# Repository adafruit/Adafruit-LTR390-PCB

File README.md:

## Adafruit LTR390 UV and Ambient Light Sensor PCB

<a href="http://www.adafruit.com/products/4831"><br/>
Click here to purchase one from the Adafruit shop</a>

PCB files for the Adafruit LTR390 UV and Ambient Light Sensor. 

Format is EagleCAD schematic and board layout
* https://www.adafruit.com/product/4831

### Description

INSERT PRODUCT COPY HERE

### License

Adafruit invests time and resources providing this open source design, please support Adafruit and open-source hardware by purchasing products from [Adafruit](https://www.adafruit.com)!

Designed by Limor Fried/Ladyada for Adafruit Industries.

Creative Commons Attribution/Share-Alike, all text above must be included in any redistribution. 
See license.txt for additional details.

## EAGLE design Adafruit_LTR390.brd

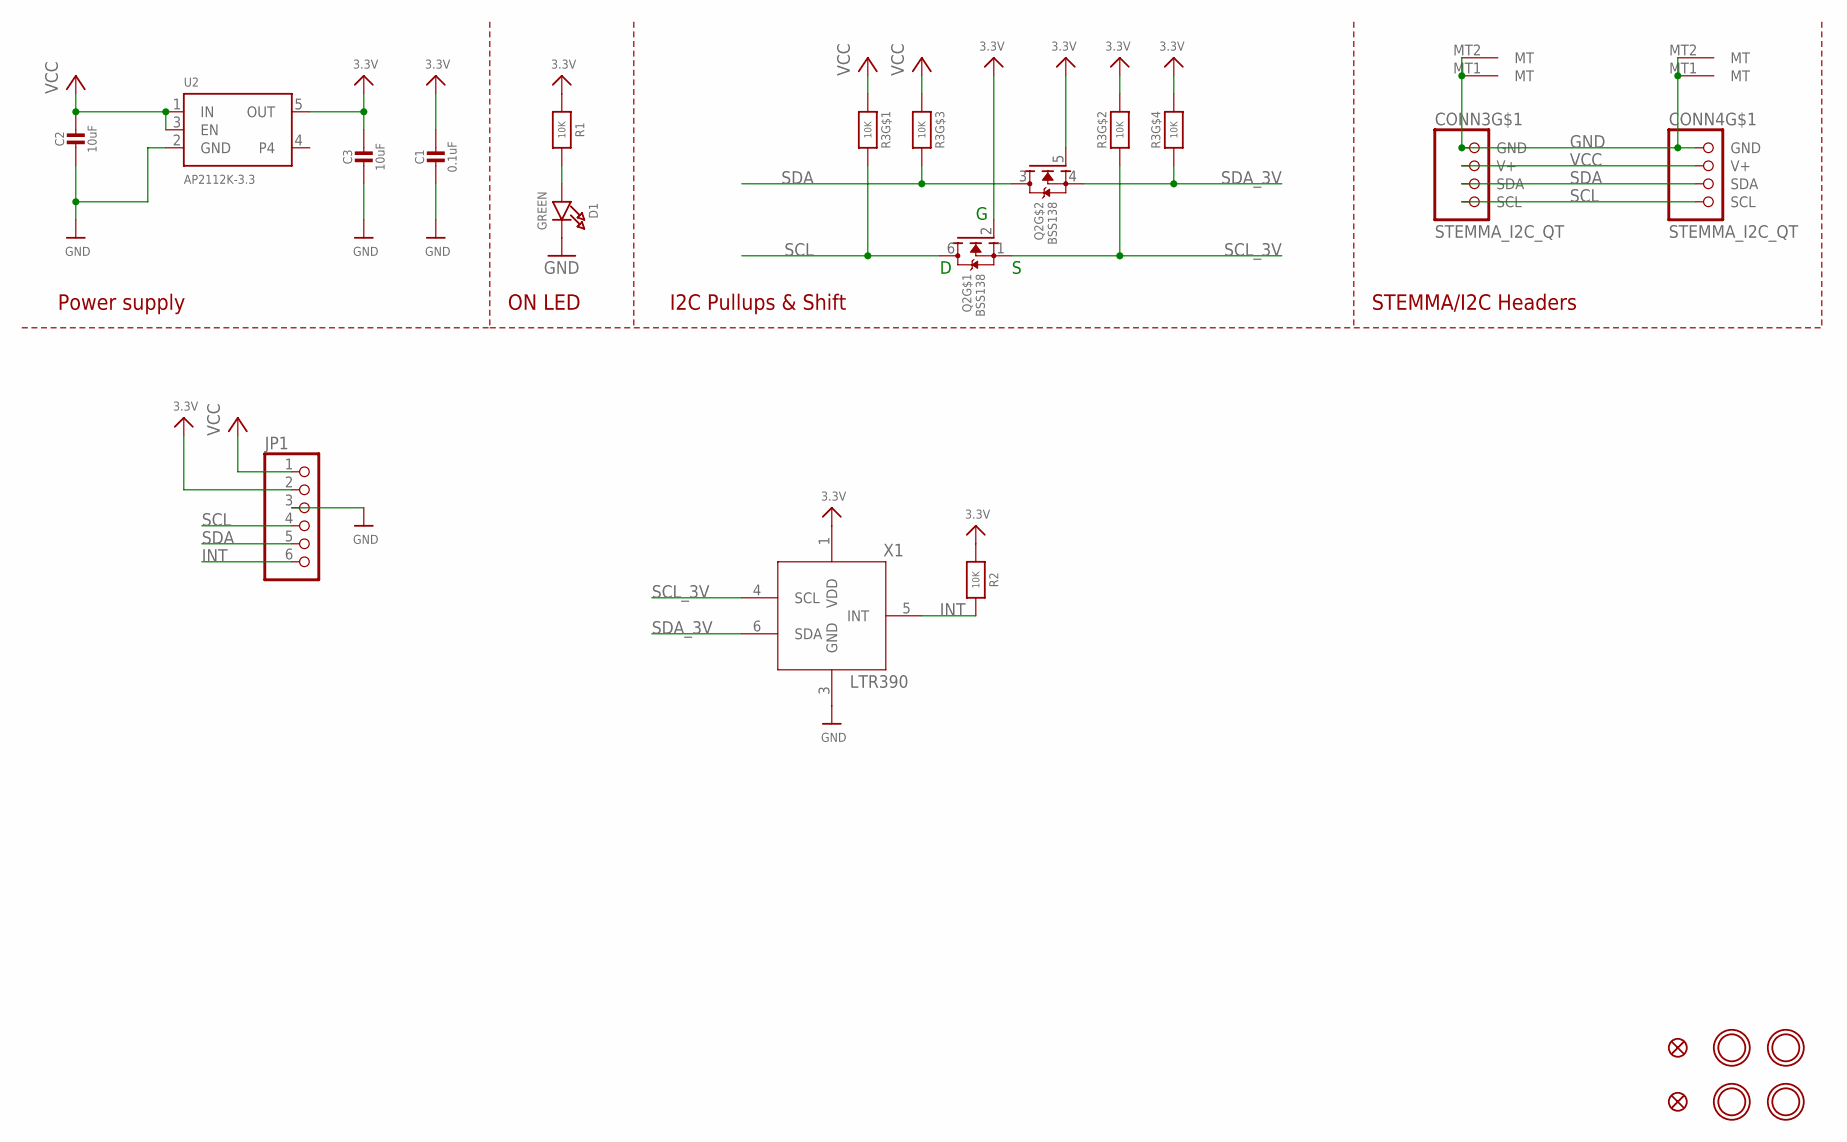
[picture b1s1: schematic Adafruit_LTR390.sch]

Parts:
C1: 0.1uF; 0603-NO
C2, C3: 10uF; 0805-NO
CONN3, CONN4: STEMMA_I2C_QT; JST_SH4
D1: GREEN; CHIPLED_0603_NOOUTLINE
FID3, FID4: FIDUCIAL_1MM
JP1: HEADER-1X670MIL; 1X06_ROUND_70
Q2: BSS138; SOT363
R1, R2: 10K; 0603-NO
R3: 10K; RESPACK_4X0603
U2: AP2112K-3.3; SOT23-5
U$1, U$17, U$19, U$21: MOUNTINGHOLE2.5; MOUNTINGHOLE_2.5_PLATED
X1: LTR390

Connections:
3.3V: C1.1, C3.1, JP1.2, Q2.2 (G), Q2.5 (G), R1.1, R2.1, R3.2 (1), R3.4 (1), U2.5 (OUT), X1.1 (VDD)
GND: C1.2, C2.2, C3.2, CONN3.1 (GND), CONN3.MT1 (MT), CONN3.MT2 (MT), CONN4.1 (GND), CONN4.MT1 (MT), CONN4.MT2 (MT), D1.C, JP1.3, U2.2 (GND), X1.3 (GND)
INT: JP1.6, R2.2, X1.5 (INT)
unnamed: D1.A, R1.2
SCL: CONN3.4 (SCL), CONN4.4 (SCL), JP1.4, Q2.6 (D), R3.8 (2)
SCL_3V: Q2.1 (S), R3.7 (2), X1.4 (SCL)
SDA: CONN3.3 (SDA), CONN4.3 (SDA), JP1.5, Q2.3 (D), R3.6 (2)
SDA_3V: Q2.4 (S), R3.5 (2), X1.6 (SDA)
VCC: C2.1, CONN3.2 (V+), CONN4.2 (V+), JP1.1, R3.1, R3.3 (1), U2.1 (IN), U2.3 (EN)

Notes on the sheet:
I2C Pullups & Shift
STEMMA/I2C Headers
ON LED
Power supply

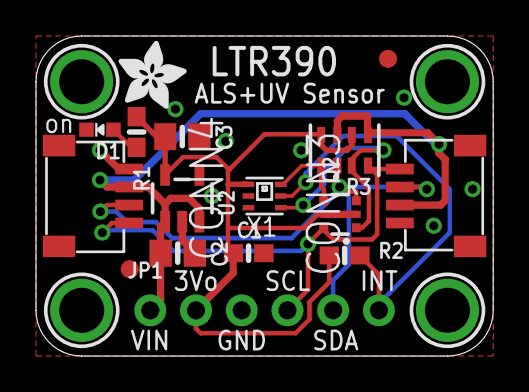
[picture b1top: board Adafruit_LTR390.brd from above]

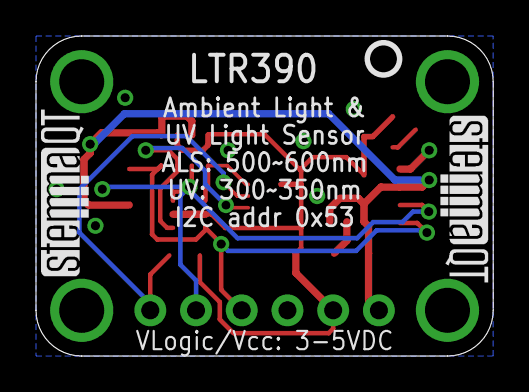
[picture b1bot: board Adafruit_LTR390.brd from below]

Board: 2 copper layers, 25.4 x 17.8 mm, 23 parts (3 on the bottom side), 9 nets.

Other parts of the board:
U$22: ADAFRUIT_3.5MM
U$25: PCBFEAT-REV-040
U$30, U$31: STEMMAQT

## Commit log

2020-12-29 initial commit of rev A

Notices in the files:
parts and their libraries:
microbuilder: This work is placed in the public domain, and may be freely used for commercial and non-commercial work with the following conditions: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
